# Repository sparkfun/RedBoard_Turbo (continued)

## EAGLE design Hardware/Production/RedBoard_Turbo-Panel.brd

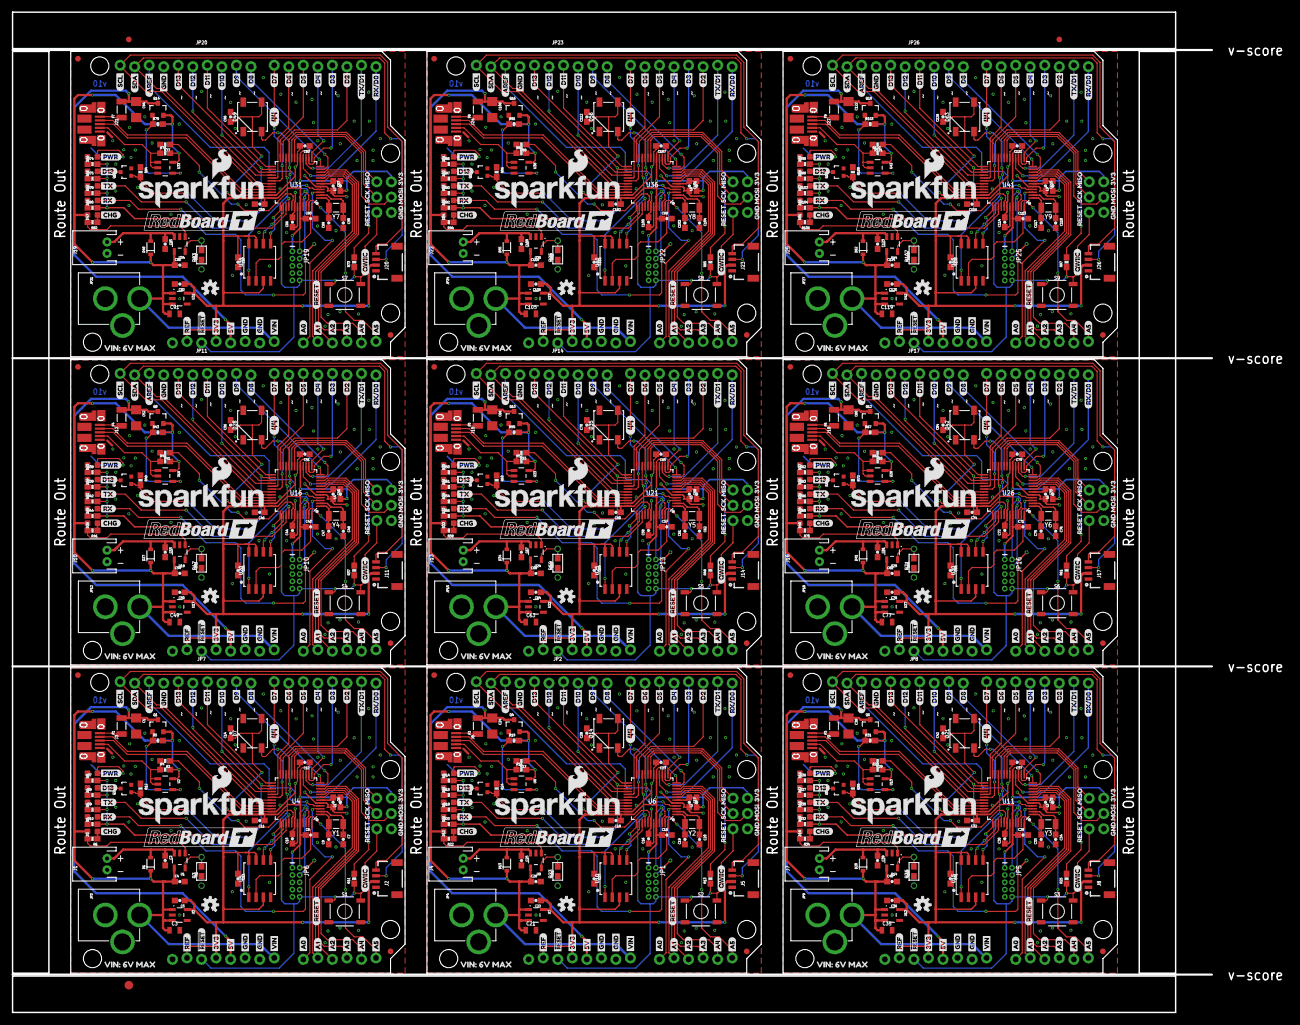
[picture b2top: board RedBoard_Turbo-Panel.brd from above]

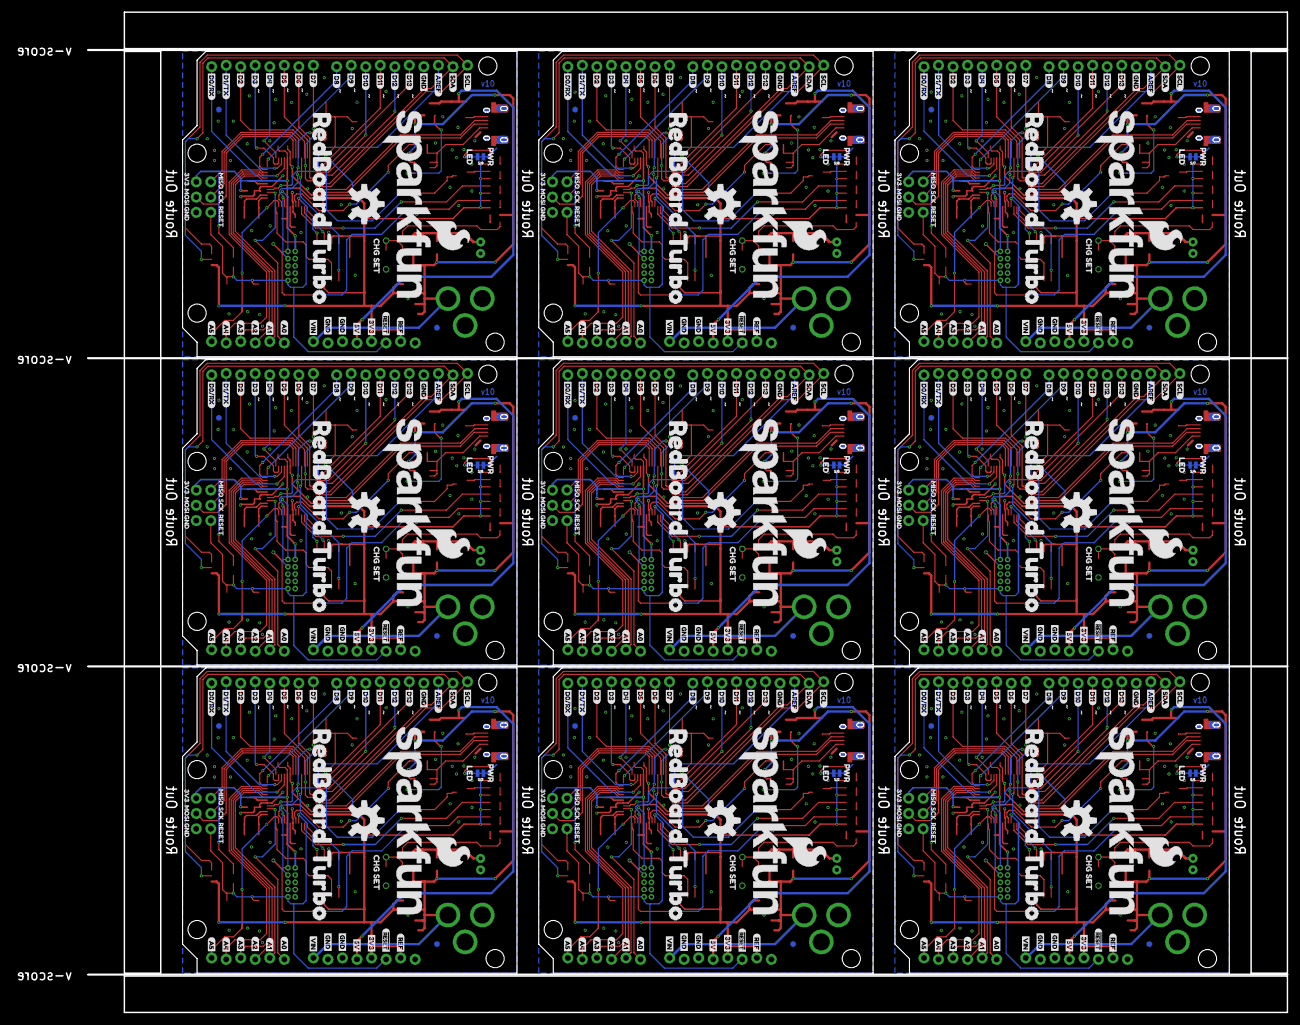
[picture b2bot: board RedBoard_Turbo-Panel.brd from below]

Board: 2 copper layers, 222.7 x 174.6 mm, 1335 parts (414 on the bottom side), 522 nets.

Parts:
C1, C24, C38, C52, C66, C80, C94, C108, C122: 2.2UF; 1206@1
C2, C4, C25, C26, C39, C40, C53, C54, C67, C68, C81, C82, C95, C96, C109, C110, C123, C124: 4.7uF; 0603-CAP
C3, C21, C35, C49, C63, C77, C91, C105, C119: 1.0uF; 0805
C5, C22, C36, C50, C64, C78, C92, C106, C120: 2.2uF; 0603-CAP
C6, C8, C10, C11, C12, C13, C14, C15, C16, C17, C18, C23, C27, C28, C29, C30, C31, C32, C37, C41, C42, C43, C44, C45, C46, C51, C55, C56, C57, C58, C59, C60, C65, C69, C70, C71, C72, C73, C74, C79, C83, C84, C85, C86, C87, C88, C93, C97, C98, C99, C100, C101, C102, C107, C111, C112, C113, C114, C115, C116, C121, C125, C126: 0.1uF; 0603-CAP
C7, C9, C19, C20, C33, C34, C47, C48, C61, C62, C75, C76, C89, C90, C103, C104, C117, C118: 15pF; 0603-CAP
D1, D13, D20, D27, D34, D41, D48, D55, D62: BAT20J; SOD-323
D2, D6, D11, D12, D18, D19, D25, D26, D32, D33, D39, D40, D46, D47, D53, D54, D60, D61: Yellow; LED-0603
D3, D9, D16, D23, D30, D37, D44, D51, D58: RED; LED-0603
D4, D10, D17, D24, D31, D38, D45, D52, D59: BLUE; LED-0603
D5, D8, D15, D22, D29, D36, D43, D50, D57: GREEN; LED-0603
D7, D14, D21, D28, D35, D42, D49, D56, D63: WS2812B
E$1, E$2: FIDUCIAL-1X2
E$3: FIDUCIAL-1.5X3
F1, F2, F3, F4, F5, F6, F7, F8, F9: 500mA; PTC-1206
FID1, FID2, FID3, FID4, FID5, FID6, FID7, FID8, FID9, FID10, FID11, FID12, FID13, FID14, FID15, FID16, FID17, FID18, FID19, FID20, FID21, FID22, FID23, FID24, FID25, FID26, FID27, FID28, FID29, FID30, FID31, FID32, FID33, FID34, FID35, FID36: FIDUCIAL1X2; FIDUCIAL-1X2
J1, J4, J7, J10, J13, J16, J19, J22, J25: JST-2-PTH
J2, J5, J8, J11, J14, J17, J20, J23, J26: 1X04_1MM_RA
J3, J6, J9, J12, J15, J18, J21, J24, J27: USB-MICROB-PTH-MILL
JP1, JP5, JP6, JP10, JP13, JP16, JP19, JP22, JP25: CORTEX_DEBUGPTH; 2X5-PTH-1.27MM
JP2, JP7, JP8, JP11, JP14, JP17, JP20, JP23, JP26: ARDUINO_UNO_R3LOCK_HOLES; ARDUINO_R3_LOCK_HOLES
JP3, JP4, JP9, JP12, JP15, JP18, JP21, JP24, JP27: POWER_JACKPTH; POWER_JACK_PTH
L1, L2, L3, L4, L5, L6, L7, L8, L9: FB - 30Ohm; 0603
LOGO1, LOGO6, LOGO10, LOGO14, LOGO18, LOGO22, LOGO26, LOGO30, LOGO34: SFE_LOGO_NAME_FLAME.2_INCH; SFE_LOGO_NAME_FLAME_.2
LOGO2, LOGO7, LOGO11, LOGO15, LOGO19, LOGO23, LOGO27, LOGO31, LOGO35: SFE_LOGO_NAME_FLAME.3_INCH; SFE_LOGO_NAME_FLAME_.3
LOGO3, LOGO5, LOGO9, LOGO13, LOGO17, LOGO21, LOGO25, LOGO29, LOGO33: OSHW-LOGOS; OSHW-LOGO-S
LOGO4, LOGO8, LOGO12, LOGO16, LOGO20, LOGO24, LOGO28, LOGO32, LOGO36: OSHW-LOGOL; OSHW-LOGO-L
Q1, Q4, Q6, Q8, Q10, Q12, Q14, Q16, Q18: 2.5A/30V; SOT23-3
Q2, Q3, Q5, Q7, Q9, Q11, Q13, Q15, Q17: 2N7002PW; SOT323
R1, R21, R33, R45, R57, R69, R81, R93, R105: 3.9K; 0603
R2, R6, R7, R8, R9, R10, R14, R15, R17, R18, R20, R22, R26, R27, R29, R30, R32, R34, R38, R39, R41, R42, R44, R46, R50, R51, R53, R54, R56, R58, R62, R63, R65, R66, R68, R70, R74, R75, R77, R78, R80, R82, R86, R87, R89, R90, R92, R94, R98, R99, R101, R102, R104, R106: 330; 0603-RES
R3, R23, R35, R47, R59, R71, R83, R95, R107: PROG; 1/6W-RES
R4, R12, R16, R24, R28, R36, R40, R48, R52, R60, R64, R72, R76, R84, R88, R96, R100, R108: 100k; 0603-RES
R5, R19, R31, R43, R55, R67, R79, R91, R103: 47K; 0603-RES
R11, R13, R25, R37, R49, R61, R73, R85, R97: 10K; 0603-RES
S1, S2, S3, S4, S5, S6, S7, S8, S9: TACTILE_SWITCH_SMD_5.2MM
SJ1, SJ2, SJ3, SJ4, SJ5, SJ6, SJ7, SJ8, SJ9: PWR-LED; PAD-JUMPER-2-NC_BY_TRACE_NO_SILK
TP1, TP2, TP3, TP4, TP5, TP6, TP7, TP8, TP9: TEST-POINTTP_15TH_THRU; TP_15TH
U1, U9, U14, U19, U24, U29, U34, U39, U44: MCP73831; SOT23-5
U2, U8, U13, U18, U23, U28, U33, U38, U43: 74AHC1G125; SOT23-5
U3, U7, U12, U17, U22, U27, U32, U37, U42: 3.3V; SOT23-5
U4, U6, U11, U16, U21, U26, U31, U36, U41: ATSAMD21G-A; TQFP-48
U5, U10, U15, U20, U25, U30, U35, U40, U45: W25Q32FV; SOIC-8
U$1, U$44, U$123, U$166, U$211, U$254, U$299, U$342, U$387, U$430, U$475, U$518, U$563, U$606, U$651, U$694, U$739, U$782: #RESET1
U$2, U$89, U$177, U$265, U$353, U$441, U$529, U$617, U$705: 3V317
U$3, U$90, U$178, U$266, U$354, U$442, U$530, U$618, U$706: 5V18
U$4, U$91, U$179, U$267, U$355, U$443, U$531, U$619, U$707: CHG30
U$5, U$92, U$180, U$268, U$356, U$444, U$532, U$620, U$708: RX#D015
U$6, U$93, U$181, U$269, U$357, U$445, U$533, U$621, U$709: TX#D114
U$7, U$94, U$182, U$270, U$358, U$446, U$534, U$622, U$710: D213
U$8, U$95, U$183, U$271, U$359, U$447, U$535, U$623, U$711: D312
U$9, U$96, U$184, U$272, U$360, U$448, U$536, U$624, U$712: D411
U$10, U$97, U$185, U$273, U$361, U$449, U$537, U$625, U$713: D510
U$11, U$98, U$186, U$274, U$362, U$450, U$538, U$626, U$714: D69
U$12, U$99, U$187, U$275, U$363, U$451, U$539, U$627, U$715: D78
U$13, U$100, U$188, U$276, U$364, U$452, U$540, U$628, U$716: D87
U$14, U$101, U$189, U$277, U$365, U$453, U$541, U$629, U$717: D96
U$15, U$102, U$190, U$278, U$366, U$454, U$542, U$630, U$718: D105
U$16, U$103, U$191, U$279, U$367, U$455, U$543, U$631, U$719: D114
U$17, U$104, U$192, U$280, U$368, U$456, U$544, U$632, U$720: D123
U$18, U$105, U$193, U$281, U$369, U$457, U$545, U$633, U$721: D132
U$19, U$36, U$37, U$106, U$121, U$122, U$194, U$209, U$210, U$282, U$297, U$298, U$370, U$385, U$386, U$458, U$473, U$474, U$546, U$561, U$562, U$634, U$649, U$650, U$722, U$737, U$738: GND16
U$20, U$81, U$107, U$164, U$195, U$252, U$283, U$340, U$371, U$428, U$459, U$516, U$547, U$604, U$635, U$692, U$723, U$780: SDA1
U$21, U$80, U$108, U$163, U$196, U$251, U$284, U$339, U$372, U$427, U$460, U$515, U$548, U$603, U$636, U$691, U$724, U$779: SCL0
U$22, U$109, U$197, U$285, U$373, U$461, U$549, U$637, U$725: TX28
U$23, U$110, U$198, U$286, U$374, U$462, U$550, U$638, U$726: RX29
U$24, U$111, U$199, U$287, U$375, U$463, U$551, U$639, U$727: PWR26
U$25, U$112, U$200, U$288, U$376, U$464, U$552, U$640, U$728: D1327
U$26, U$124, U$212, U$300, U$388, U$476, U$564, U$652, U$740: REF0
U$27, U$53, U$125, U$139, U$213, U$227, U$301, U$315, U$389, U$403, U$477, U$491, U$565, U$579, U$653, U$667, U$741, U$755: AREF2
U$28, U$113, U$201, U$289, U$377, U$465, U$553, U$641, U$729: QWIIC31
U$29, U$114, U$202, U$290, U$378, U$466, U$554, U$642, U$730: A020
U$30, U$115, U$203, U$291, U$379, U$467, U$555, U$643, U$731: A121
U$31, U$116, U$204, U$292, U$380, U$468, U$556, U$644, U$732: A222
U$32, U$117, U$205, U$293, U$381, U$469, U$557, U$645, U$733: A323
U$33, U$118, U$206, U$294, U$382, U$470, U$558, U$646, U$734: A424
U$34, U$119, U$207, U$295, U$383, U$471, U$559, U$647, U$735: A525
U$35, U$120, U$208, U$296, U$384, U$472, U$560, U$648, U$736: VIN19
U$38, U$126, U$214, U$302, U$390, U$478, U$566, U$654, U$742: GND7
U$39, U$127, U$215, U$303, U$391, U$479, U$567, U$655, U$743: MOSI4
U$40, U$128, U$216, U$304, U$392, U$480, U$568, U$656, U$744: 3V36
U$41, U$129, U$217, U$305, U$393, U$481, U$569, U$657, U$745: SCK5
U$42, U$130, U$218, U$306, U$394, U$482, U$570, U$658, U$746: MISO3
U$43, U$83, U$131, U$169, U$219, U$257, U$307, U$345, U$395, U$433, U$483, U$521, U$571, U$609, U$659, U$697, U$747, U$785: RESET0
U$45, U$132, U$220, U$308, U$396, U$484, U$572, U$660, U$748: 3V325
U$46, U$167, U$255, U$343, U$431, U$519, U$607, U$695, U$783: 3V30
U$47, U$133, U$221, U$309, U$397, U$485, U$573, U$661, U$749: A018
U$48, U$134, U$222, U$310, U$398, U$486, U$574, U$662, U$750: A119
U$49, U$135, U$223, U$311, U$399, U$487, U$575, U$663, U$751: A220
U$50, U$136, U$224, U$312, U$400, U$488, U$576, U$664, U$752: A321
U$51, U$137, U$225, U$313, U$401, U$489, U$577, U$665, U$753: A422
U$52, U$138, U$226, U$314, U$402, U$490, U$578, U$666, U$754: A523
U$54, U$174, U$262, U$350, U$438, U$526, U$614, U$702, U$790: LED1
U$55, U$140, U$228, U$316, U$404, U$492, U$580, U$668, U$756: D0#RX17
U$56, U$141, U$229, U$317, U$405, U$493, U$581, U$669, U$757: D1#TX15
U$57, U$168, U$256, U$344, U$432, U$520, U$608, U$696, U$784: 5V26
U$58, U$142, U$230, U$318, U$406, U$494, U$582, U$670, U$758: D79
U$59, U$143, U$231, U$319, U$407, U$495, U$583, U$671, U$759: D88
U$60, U$144, U$232, U$320, U$408, U$496, U$584, U$672, U$760: D97
U$61, U$145, U$233, U$321, U$409, U$497, U$585, U$673, U$761: D106
U$62, U$146, U$234, U$322, U$410, U$498, U$586, U$674, U$762: D115
U$63, U$147, U$235, U$323, U$411, U$499, U$587, U$675, U$763: D124
U$64, U$148, U$236, U$324, U$412, U$500, U$588, U$676, U$764: D133
U$65, U$149, U$237, U$325, U$413, U$501, U$589, U$677, U$765: D214
U$66, U$150, U$238, U$326, U$414, U$502, U$590, U$678, U$766: D313
U$67, U$151, U$239, U$327, U$415, U$503, U$591, U$679, U$767: D412
U$68, U$152, U$240, U$328, U$416, U$504, U$592, U$680, U$768: D511
U$69, U$153, U$241, U$329, U$417, U$505, U$593, U$681, U$769: D610
U$70, U$71, U$72, U$154, U$155, U$156, U$242, U$243, U$244, U$330, U$331, U$332, U$418, U$419, U$420, U$506, U$507, U$508, U$594, U$595, U$596, U$682, U$683, U$684, U$770, U$771, U$772: GND24
U$73, U$157, U$245, U$333, U$421, U$509, U$597, U$685, U$773: GND33
U$74, U$175, U$263, U$351, U$439, U$527, U$615, U$703, U$791: PWR0
U$75, U$158, U$246, U$334, U$422, U$510, U$598, U$686, U$774: MISO30
U$76, U$159, U$247, U$335, U$423, U$511, U$599, U$687, U$775: MOSI34
U$77, U$160, U$248, U$336, U$424, U$512, U$600, U$688, U$776: REF28
U$78, U$161, U$249, U$337, U$425, U$513, U$601, U$689, U$777: RESET32
U$79, U$162, U$250, U$338, U$426, U$514, U$602, U$690, U$778: SCK31
U$82, U$165, U$253, U$341, U$429, U$517, U$605, U$693, U$781: VIN27
U$84, U$171, U$259, U$347, U$435, U$523, U$611, U$699, U$787: 440
U$85, U$172, U$260, U$348, U$436, U$524, U$612, U$700, U$788: REDBOARD_TURBO1
U$86, U$170, U$258, U$346, U$434, U$522, U$610, U$698, U$786: BITMAP#JPG
U$87, U$173, U$261, U$349, U$437, U$525, U$613, U$701, U$789: CHG_SET1
U$88, U$176, U$264, U$352, U$440, U$528, U$616, U$704, U$792: VIN#_6V_MAX2
Y1, Y2, Y3, Y4, Y5, Y6, Y7, Y8, Y9: 32.768kHz; CRYSTAL-SMD-3.2X1.5MM

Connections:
3.3V: C5.1, C8.1, C11.1, C12.1, C13.1, C14.1, D7.1, J2.2, JP6.1, JP7.3.3V, JP7.IOREF, JP7.VCC, L1.1, R7.2, R8.2, R9.2, R10.2, R11.2, U3.5, U4.17, U4.36, U4.44, U5.3, U5.7, U5.8
3.3V1: C15.1, C18.1, C22.1, C23.1, C27.1, C28.1, D14.1, J5.2, JP1.1, JP2.3.3V, JP2.IOREF, JP2.VCC, L2.1, R13.2, R14.2, R15.2, R18.2, R20.2, U6.17, U6.36, U6.44, U7.5, U10.3, U10.7, U10.8
3.3V2: C29.1, C32.1, C36.1, C37.1, C41.1, C42.1, D21.1, J8.2, JP5.1, JP8.3.3V, JP8.IOREF, JP8.VCC, L3.1, R25.2, R26.2, R27.2, R30.2, R32.2, U11.17, U11.36, U11.44, U12.5, U15.3, U15.7, U15.8
3.3V3: C43.1, C46.1, C50.1, C51.1, C55.1, C56.1, D28.1, J11.2, JP10.1, JP11.3.3V, JP11.IOREF, JP11.VCC, L4.1, R37.2, R38.2, R39.2, R42.2, R44.2, U16.17, U16.36, U16.44, U17.5, U20.3, U20.7, U20.8
3.3V4: C57.1, C60.1, C64.1, C65.1, C69.1, C70.1, D35.1, J14.2, JP13.1, JP14.3.3V, JP14.IOREF, JP14.VCC, L5.1, R49.2, R50.2, R51.2, R54.2, R56.2, U21.17, U21.36, U21.44, U22.5, U25.3, U25.7, U25.8
3.3V5: C71.1, C74.1, C78.1, C79.1, C83.1, C84.1, D42.1, J17.2, JP16.1, JP17.3.3V, JP17.IOREF, JP17.VCC, L6.1, R61.2, R62.2, R63.2, R66.2, R68.2, U26.17, U26.36, U26.44, U27.5, U30.3, U30.7, U30.8
3.3V6: C85.1, C88.1, C92.1, C93.1, C97.1, C98.1, D49.1, J20.2, JP19.1, JP20.3.3V, JP20.IOREF, JP20.VCC, L7.1, R73.2, R74.2, R75.2, R78.2, R80.2, U31.17, U31.36, U31.44, U32.5, U35.3, U35.7, U35.8
3.3V7: C99.1, C102.1, C106.1, C107.1, C111.1, C112.1, D56.1, J23.2, JP22.1, JP23.3.3V, JP23.IOREF, JP23.VCC, L8.1, R85.2, R86.2, R87.2, R90.2, R92.2, U36.17, U36.36, U36.44, U37.5, U40.3, U40.7, U40.8
3.3V8: C113.1, C116.1, C120.1, C121.1, C125.1, C126.1, D63.1, J26.2, JP25.1, JP26.3.3V, JP26.IOREF, JP26.VCC, L9.1, R97.2, R98.2, R99.2, R102.2, R104.2, U41.17, U41.36, U41.44, U42.5, U45.3, U45.7, U45.8
!RESET: JP6.10, JP7.RESET@1, JP7.RESET@2, R11.1, S1.1, S1.2, U4.40
!RESET1: JP1.10, JP2.RESET@1, JP2.RESET@2, R13.1, S2.1, S2.2, U6.40
!RESET2: JP5.10, JP8.RESET@1, JP8.RESET@2, R25.1, S3.1, S3.2, U11.40
!RESET3: JP10.10, JP11.RESET@1, JP11.RESET@2, R37.1, S4.1, S4.2, U16.40
!RESET4: JP13.10, JP14.RESET@1, JP14.RESET@2, R49.1, S5.1, S5.2, U21.40
!RESET5: JP16.10, JP17.RESET@1, JP17.RESET@2, R61.1, S6.1, S6.2, U26.40
!RESET6: JP19.10, JP20.RESET@1, JP20.RESET@2, R73.1, S7.1, S7.2, U31.40
!RESET7: JP22.10, JP23.RESET@1, JP23.RESET@2, R85.1, S8.1, S8.2, U36.40
!RESET8: JP25.10, JP26.RESET@1, JP26.RESET@2, R97.1, S9.1, S9.2, U41.40
A0: JP7.A0, U4.3
A1: JP7.A1, U4.7
A2: JP7.A2, U4.8
A3: JP7.A3, U4.9
A4: JP7.A4, U4.10
A5: JP7.A5, U4.47
A6: JP2.A3, U6.9
A7: JP2.A2, U6.8
A8: JP2.A1, U6.7
A9: JP2.A0, U6.3
A10: JP2.A4, U6.10
A11: JP2.A5, U6.47
A12: JP8.A3, U11.9
A13: JP8.A2, U11.8
A14: JP8.A1, U11.7
A15: JP8.A0, U11.3
A16: JP8.A4, U11.10
A17: JP8.A5, U11.47
A18: JP11.A3, U16.9
A19: JP11.A2, U16.8
A20: JP11.A1, U16.7
A21: JP11.A0, U16.3
A22: JP11.A4, U16.10
A23: JP11.A5, U16.47
A24: JP14.A3, U21.9
A25: JP14.A2, U21.8
A26: JP14.A1, U21.7
A27: JP14.A0, U21.3
A28: JP14.A4, U21.10
A29: JP14.A5, U21.47
A30: JP17.A3, U26.9
A31: JP17.A2, U26.8
A32: JP17.A1, U26.7
A33: JP17.A0, U26.3
A34: JP17.A4, U26.10
A35: JP17.A5, U26.47
A36: JP20.A3, U31.9
A37: JP20.A2, U31.8
A38: JP20.A1, U31.7
A39: JP20.A0, U31.3
A40: JP20.A4, U31.10
A41: JP20.A5, U31.47
A42: JP23.A3, U36.9
A43: JP23.A2, U36.8
A44: JP23.A1, U36.7
A45: JP23.A0, U36.3
A46: JP23.A4, U36.10
A47: JP23.A5, U36.47
A48: JP26.A3, U41.9
A49: JP26.A2, U41.8
A50: JP26.A1, U41.7
A51: JP26.A0, U41.3
A52: JP26.A4, U41.10
A53: JP26.A5, U41.47
AREF: JP7.AREF, U4.4
AREF1: JP2.AREF, U6.4
AREF2: JP8.AREF, U11.4
AREF3: JP11.AREF, U16.4
AREF4: JP14.AREF, U21.4
AREF5: JP17.AREF, U26.4
AREF6: JP20.AREF, U31.4
AREF7: JP23.AREF, U36.4
AREF8: JP26.AREF, U41.4
CHG_STAT: R6.2, U1.1
CHG_STAT1: R22.2, U9.1
CHG_STAT2: R34.2, U14.1
CHG_STAT3: R46.2, U19.1
CHG_STAT4: R58.2, U24.1
CHG_STAT5: R70.2, U29.1
CHG_STAT6: R82.2, U34.1
CHG_STAT7: R94.2, U39.1
CHG_STAT8: R106.2, U44.1
D0/RXI: JP7.D0, U4.16
D0/RXI1: JP2.D0, U6.16
D0/RXI2: JP8.D0, U11.16
D0/RXI3: JP11.D0, U16.16
D0/RXI4: JP14.D0, U21.16
D0/RXI5: JP17.D0, U26.16
D0/RXI6: JP20.D0, U31.16
D0/RXI7: JP23.D0, U36.16
D0/RXI8: JP26.D0, U41.16
D1: JP2.D4, U6.13
D1/TXO: JP7.D1, U4.15
D1/TXO1: JP2.D1, U6.15
D1/TXO2: JP8.D1, U11.15
D1/TXO3: JP11.D1, U16.15
D1/TXO4: JP14.D1, U21.15
D1/TXO5: JP17.D1, U26.15
D1/TXO6: JP20.D1, U31.15
D1/TXO7: JP23.D1, U36.15
D1/TXO8: JP26.D1, U41.15
D2: JP7.D2, U4.23
D3: JP7.D3, U4.14
D4: JP7.D4, U4.13
D5: JP7.D5, U4.24
D6: JP7.D6, U4.29
D7: JP7.D7, U4.30
D8: JP7.D8, U4.11
D9: JP7.D9, U4.12
D10: JP7.D10, U4.27
D11: JP7.D11, U4.25
D12: JP7.D12, U4.28
D13: JP7.D13, Q2.1, R12.2, U4.26
D14: JP2.D3, U6.14
D15: JP2.D2, U6.23
D16: JP2.D5, U6.24
D17: JP2.D6, U6.29
D18: JP2.D7, U6.30
D19: JP2.D8, U6.11
D20: JP2.D9, U6.12
D21: JP2.D12, U6.28
D22: JP2.D11, U6.25
D23: JP2.D10, U6.27
D24: JP2.D13, Q3.1, R24.2, U6.26
D25: JP8.D4, U11.13
D26: JP8.D3, U11.14
D27: JP8.D2, U11.23
D28: JP8.D5, U11.24
D29: JP8.D6, U11.29
D30: JP8.D7, U11.30
D31: JP8.D8, U11.11
D32: JP8.D9, U11.12
D33: JP8.D12, U11.28
D34: JP8.D11, U11.25
D35: JP8.D10, U11.27
D36: JP8.D13, Q5.1, R36.2, U11.26
D37: JP11.D4, U16.13
D38: JP11.D3, U16.14
D39: JP11.D2, U16.23
D40: JP11.D5, U16.24
D41: JP11.D6, U16.29
D42: JP11.D7, U16.30
D43: JP11.D8, U16.11
D44: JP11.D9, U16.12
D45: JP11.D12, U16.28
D46: JP11.D11, U16.25
D47: JP11.D10, U16.27
D48: JP11.D13, Q7.1, R48.2, U16.26
D49: JP14.D4, U21.13
D50: JP14.D3, U21.14
D51: JP14.D2, U21.23
D52: JP14.D5, U21.24
D53: JP14.D6, U21.29
D54: JP14.D7, U21.30
D55: JP14.D8, U21.11
D56: JP14.D9, U21.12
D57: JP14.D12, U21.28
D58: JP14.D11, U21.25
D59: JP14.D10, U21.27
D60: JP14.D13, Q9.1, R60.2, U21.26
D61: JP17.D4, U26.13
D62: JP17.D3, U26.14
D63: JP17.D2, U26.23
D64: JP17.D5, U26.24
D65: JP17.D6, U26.29
D66: JP17.D7, U26.30
D67: JP17.D8, U26.11
D68: JP17.D9, U26.12
D69: JP17.D12, U26.28
D70: JP17.D11, U26.25
D71: JP17.D10, U26.27
D72: JP17.D13, Q11.1, R72.2, U26.26
D73: JP20.D4, U31.13
D74: JP20.D3, U31.14
D75: JP20.D2, U31.23
D76: JP20.D5, U31.24
D77: JP20.D6, U31.29
D78: JP20.D7, U31.30
D79: JP20.D8, U31.11
D80: JP20.D9, U31.12
D81: JP20.D12, U31.28
D82: JP20.D11, U31.25
D83: JP20.D10, U31.27
D84: JP20.D13, Q13.1, R84.2, U31.26
D85: JP23.D4, U36.13
D86: JP23.D3, U36.14
D87: JP23.D2, U36.23
D88: JP23.D5, U36.24
D89: JP23.D6, U36.29
D90: JP23.D7, U36.30
D91: JP23.D8, U36.11
D92: JP23.D9, U36.12
D93: JP23.D12, U36.28
D94: JP23.D11, U36.25
D95: JP23.D10, U36.27
D96: JP23.D13, Q15.1, R96.2, U36.26
D97: JP26.D4, U41.13
D98: JP26.D3, U41.14
D99: JP26.D2, U41.23
D100: JP26.D5, U41.24
D101: JP26.D6, U41.29
D102: JP26.D7, U41.30
D103: JP26.D8, U41.11
D104: JP26.D9, U41.12
D105: JP26.D12, U41.28
D106: JP26.D11, U41.25
D107: JP26.D10, U41.27
D108: JP26.D13, Q17.1, R108.2, U41.26
FLASH_CS: U4.22, U5.1
FLASH_CS1: U6.22, U10.1
FLASH_CS2: U11.22, U15.1
FLASH_CS3: U16.22, U20.1
FLASH_CS4: U21.22, U25.1
FLASH_CS5: U26.22, U30.1
FLASH_CS6: U31.22, U35.1
FLASH_CS7: U36.22, U40.1
FLASH_CS8: U41.22, U45.1
FLASH_MISO: U4.48, U5.2
FLASH_MISO1: U6.48, U10.2
FLASH_MISO2: U11.48, U15.2
FLASH_MISO3: U16.48, U20.2
FLASH_MISO4: U21.48, U25.2
FLASH_MISO5: U26.48, U30.2
FLASH_MISO6: U31.48, U35.2
FLASH_MISO7: U36.48, U40.2
FLASH_MISO8: U41.48, U45.2
FLASH_MOSI: U4.37, U5.5
FLASH_MOSI1: U6.37, U10.5
FLASH_MOSI2: U11.37, U15.5
FLASH_MOSI3: U16.37, U20.5
FLASH_MOSI4: U21.37, U25.5
FLASH_MOSI5: U26.37, U30.5
FLASH_MOSI6: U31.37, U35.5
FLASH_MOSI7: U36.37, U40.5
FLASH_MOSI8: U41.37, U45.5
FLASH_SCK: U4.38, U5.6
FLASH_SCK1: U6.38, U10.6
FLASH_SCK2: U11.38, U15.6
FLASH_SCK3: U16.38, U20.6
FLASH_SCK4: U21.38, U25.6
FLASH_SCK5: U26.38, U30.6
FLASH_SCK6: U31.38, U35.6
FLASH_SCK7: U36.38, U40.6
FLASH_SCK8: U41.38, U45.6
GND: C1.2, C2.2, C3.2, C4.2, C5.2, C6.2, C7.2, C8.2, C9.1, C10.2, C11.2, C12.2, C13.2, C14.2, D7.3, J1.1, J2.1, J3.GND, J3.SHIELD, J3.SHIELD2, J3.SHIELD3, J3.SHIELD4, J3.SHIELD5, J3.SHIELD6, J3.SHIELD7, J3.SHIELD8, J3.SHIELD9, J3.SHIELD10, JP3.GND, JP3.GNDBREAK, JP6.3, JP6.5, JP7.GND@1, JP7.GND@2, JP7.GND@3, JP7.GND@4, Q2.2, R1.1, R3.1, R12.1, S1.3, S1.4, SJ1.1, U1.2, U2.3, U3.2, U4.5, U4.18, U4.35, U4.42, U5.4
GND1: C15.2, C16.2, C17.2, C18.2, C19.1, C20.2, C21.2, C22.2, C23.2, C24.2, C25.2, C26.2, C27.2, C28.2, D14.3, J4.1, J5.1, J6.GND, J6.SHIELD, J6.SHIELD2, J6.SHIELD3, J6.SHIELD4, J6.SHIELD5, J6.SHIELD6, J6.SHIELD7, J6.SHIELD8, J6.SHIELD9, J6.SHIELD10, JP1.3, JP1.5, JP2.GND@1, JP2.GND@2, JP2.GND@3, JP2.GND@4, JP4.GND, JP4.GNDBREAK, Q3.2, R21.1, R23.1, R24.1, S2.3, S2.4, SJ2.1, U6.5, U6.18, U6.35, U6.42, U7.2, U8.3, U9.2, U10.4
GND2: C29.2, C30.2, C31.2, C32.2, C33.1, C34.2, C35.2, C36.2, C37.2, C38.2, C39.2, C40.2, C41.2, C42.2, D21.3, J7.1, J8.1, J9.GND, J9.SHIELD, J9.SHIELD2, J9.SHIELD3, J9.SHIELD4, J9.SHIELD5, J9.SHIELD6, J9.SHIELD7, J9.SHIELD8, J9.SHIELD9, J9.SHIELD10, JP5.3, JP5.5, JP8.GND@1, JP8.GND@2, JP8.GND@3, JP8.GND@4, JP9.GND, JP9.GNDBREAK, Q5.2, R33.1, R35.1, R36.1, S3.3, S3.4, SJ3.1, U11.5, U11.18, U11.35, U11.42, U12.2, U13.3, U14.2, U15.4
GND3: C43.2, C44.2, C45.2, C46.2, C47.1, C48.2, C49.2, C50.2, C51.2, C52.2, C53.2, C54.2, C55.2, C56.2, D28.3, J10.1, J11.1, J12.GND, J12.SHIELD, J12.SHIELD2, J12.SHIELD3, J12.SHIELD4, J12.SHIELD5, J12.SHIELD6, J12.SHIELD7, J12.SHIELD8, J12.SHIELD9, J12.SHIELD10, JP10.3, JP10.5, JP11.GND@1, JP11.GND@2, JP11.GND@3, JP11.GND@4, JP12.GND, JP12.GNDBREAK, Q7.2, R45.1, R47.1, R48.1, S4.3, S4.4, SJ4.1, U16.5, U16.18, U16.35, U16.42, U17.2, U18.3, U19.2, U20.4
GND4: C57.2, C58.2, C59.2, C60.2, C61.1, C62.2, C63.2, C64.2, C65.2, C66.2, C67.2, C68.2, C69.2, C70.2, D35.3, J13.1, J14.1, J15.GND, J15.SHIELD, J15.SHIELD2, J15.SHIELD3, J15.SHIELD4, J15.SHIELD5, J15.SHIELD6, J15.SHIELD7, J15.SHIELD8, J15.SHIELD9, J15.SHIELD10, JP13.3, JP13.5, JP14.GND@1, JP14.GND@2, JP14.GND@3, JP14.GND@4, JP15.GND, JP15.GNDBREAK, Q9.2, R57.1, R59.1, R60.1, S5.3, S5.4, SJ5.1, U21.5, U21.18, U21.35, U21.42, U22.2, U23.3, U24.2, U25.4
GND5: C71.2, C72.2, C73.2, C74.2, C75.1, C76.2, C77.2, C78.2, C79.2, C80.2, C81.2, C82.2, C83.2, C84.2, D42.3, J16.1, J17.1, J18.GND, J18.SHIELD, J18.SHIELD2, J18.SHIELD3, J18.SHIELD4, J18.SHIELD5, J18.SHIELD6, J18.SHIELD7, J18.SHIELD8, J18.SHIELD9, J18.SHIELD10, JP16.3, JP16.5, JP17.GND@1, JP17.GND@2, JP17.GND@3, JP17.GND@4, JP18.GND, JP18.GNDBREAK, Q11.2, R69.1, R71.1, R72.1, S6.3, S6.4, SJ6.1, U26.5, U26.18, U26.35, U26.42, U27.2, U28.3, U29.2, U30.4
GND6: C85.2, C86.2, C87.2, C88.2, C89.1, C90.2, C91.2, C92.2, C93.2, C94.2, C95.2, C96.2, C97.2, C98.2, D49.3, J19.1, J20.1, J21.GND, J21.SHIELD, J21.SHIELD2, J21.SHIELD3, J21.SHIELD4, J21.SHIELD5, J21.SHIELD6, J21.SHIELD7, J21.SHIELD8, J21.SHIELD9, J21.SHIELD10, JP19.3, JP19.5, JP20.GND@1, JP20.GND@2, JP20.GND@3, JP20.GND@4, JP21.GND, JP21.GNDBREAK, Q13.2, R81.1, R83.1, R84.1, S7.3, S7.4, SJ7.1, U31.5, U31.18, U31.35, U31.42, U32.2, U33.3, U34.2, U35.4
GND7: C99.2, C100.2, C101.2, C102.2, C103.1, C104.2, C105.2, C106.2, C107.2, C108.2, C109.2, C110.2, C111.2, C112.2, D56.3, J22.1, J23.1, J24.GND, J24.SHIELD, J24.SHIELD2, J24.SHIELD3, J24.SHIELD4, J24.SHIELD5, J24.SHIELD6, J24.SHIELD7, J24.SHIELD8, J24.SHIELD9, J24.SHIELD10, JP22.3, JP22.5, JP23.GND@1, JP23.GND@2, JP23.GND@3, JP23.GND@4, JP24.GND, JP24.GNDBREAK, Q15.2, R93.1, R95.1, R96.1, S8.3, S8.4, SJ8.1, U36.5, U36.18, U36.35, U36.42, U37.2, U38.3, U39.2, U40.4
GND8: C113.2, C114.2, C115.2, C116.2, C117.1, C118.2, C119.2, C120.2, C121.2, C122.2, C123.2, C124.2, C125.2, C126.2, D63.3, J25.1, J26.1, J27.GND, J27.SHIELD, J27.SHIELD2, J27.SHIELD3, J27.SHIELD4, J27.SHIELD5, J27.SHIELD6, J27.SHIELD7, J27.SHIELD8, J27.SHIELD9, J27.SHIELD10, JP25.3, JP25.5, JP26.GND@1, JP26.GND@2, JP26.GND@3, JP26.GND@4, JP27.GND, JP27.GNDBREAK, Q17.2, R105.1, R107.1, R108.1, S9.3, S9.4, SJ9.1, U41.5, U41.18, U41.35, U41.42, U42.2, U43.3, U44.2, U45.4
LED/SWCLK: D7.4, JP6.4, U4.45
LED/SWCLK1: D14.4, JP1.4, U6.45
LED/SWCLK2: D21.4, JP5.4, U11.45
LED/SWCLK3: D28.4, JP10.4, U16.45
LED/SWCLK4: D35.4, JP13.4, U21.45
LED/SWCLK5: D42.4, JP16.4, U26.45
LED/SWCLK6: D49.4, JP19.4, U31.45
LED/SWCLK7: D56.4, JP22.4, U36.45
LED/SWCLK8: D63.4, JP25.4, U41.45
unnamed: F1.1, J3.VBUS
unnamed: C9.2, U4.1, Y1.P$2
unnamed: D4.C, Q2.3
unnamed: C7.1, U4.2, Y1.P$1
unnamed: D3.A, R7.1
unnamed: D4.A, R8.1
unnamed: C19.2, U6.1, Y2.P$2
unnamed: D2.C, R6.1
unnamed: C20.1, U6.2, Y2.P$1
unnamed: D5.A, R9.1
unnamed: D6.A, R10.1
unnamed: D3.C, SJ1.2
unnamed: R1.2, R3.2, U1.5
unnamed: D9.A, R14.1
unnamed: D10.A, R15.1
unnamed: D10.C, Q3.3
unnamed: F2.1, J6.VBUS
unnamed: D8.A, R18.1
unnamed: D11.A, R20.1
unnamed: D9.C, SJ2.2
unnamed: R21.2, R23.2, U9.5
unnamed: D12.C, R22.1
unnamed: C33.2, U11.1, Y3.P$2
unnamed: C34.1, U11.2, Y3.P$1
unnamed: D16.A, R26.1
unnamed: D17.A, R27.1
unnamed: D17.C, Q5.3
unnamed: F3.1, J9.VBUS
unnamed: D15.A, R30.1
unnamed: D18.A, R32.1
unnamed: D16.C, SJ3.2
unnamed: R33.2, R35.2, U14.5
unnamed: D19.C, R34.1
unnamed: C47.2, U16.1, Y4.P$2
unnamed: C48.1, U16.2, Y4.P$1
unnamed: D23.A, R38.1
unnamed: D24.A, R39.1
unnamed: D24.C, Q7.3
unnamed: F4.1, J12.VBUS
unnamed: D22.A, R42.1
unnamed: D25.A, R44.1
unnamed: D23.C, SJ4.2
unnamed: R45.2, R47.2, U19.5
unnamed: D26.C, R46.1
unnamed: C61.2, U21.1, Y5.P$2
unnamed: C62.1, U21.2, Y5.P$1
unnamed: D30.A, R50.1
unnamed: D31.A, R51.1
unnamed: D31.C, Q9.3
unnamed: F5.1, J15.VBUS
unnamed: D29.A, R54.1
unnamed: D32.A, R56.1
unnamed: D30.C, SJ5.2
unnamed: R57.2, R59.2, U24.5
unnamed: D33.C, R58.1
unnamed: C75.2, U26.1, Y6.P$2
unnamed: C76.1, U26.2, Y6.P$1
unnamed: D37.A, R62.1
unnamed: D38.A, R63.1
unnamed: D38.C, Q11.3
unnamed: F6.1, J18.VBUS
unnamed: D36.A, R66.1
unnamed: D39.A, R68.1
unnamed: D37.C, SJ6.2
unnamed: R69.2, R71.2, U29.5
unnamed: D40.C, R70.1
unnamed: C89.2, U31.1, Y7.P$2
unnamed: C90.1, U31.2, Y7.P$1
unnamed: D44.A, R74.1
unnamed: D45.A, R75.1
unnamed: D45.C, Q13.3
unnamed: F7.1, J21.VBUS
unnamed: D43.A, R78.1
unnamed: D46.A, R80.1
unnamed: D44.C, SJ7.2
unnamed: R81.2, R83.2, U34.5
unnamed: D47.C, R82.1
unnamed: C103.2, U36.1, Y8.P$2
unnamed: C104.1, U36.2, Y8.P$1
unnamed: D51.A, R86.1
unnamed: D52.A, R87.1
unnamed: D52.C, Q15.3
unnamed: F8.1, J24.VBUS
unnamed: D50.A, R90.1
unnamed: D53.A, R92.1
unnamed: D51.C, SJ8.2
unnamed: R93.2, R95.2, U39.5
unnamed: D54.C, R94.1
unnamed: C117.2, U41.1, Y9.P$2
unnamed: C118.1, U41.2, Y9.P$1
unnamed: D58.A, R98.1
unnamed: D59.A, R99.1
unnamed: D59.C, Q17.3
unnamed: F9.1, J27.VBUS
unnamed: D57.A, R102.1
unnamed: D60.A, R104.1
unnamed: D58.C, SJ9.2
unnamed: R105.2, R107.2, U44.5
unnamed: D61.C, R106.1
RX_LED/SWDIO: D6.C, JP6.2, TP1.P$1, U4.46
RX_LED/SWDIO1: D11.C, JP1.2, TP2.P$1, U6.46
RX_LED/SWDIO2: D18.C, JP5.2, TP3.P$1, U11.46
RX_LED/SWDIO3: D25.C, JP10.2, TP4.P$1, U16.46
RX_LED/SWDIO4: D32.C, JP13.2, TP5.P$1, U21.46
RX_LED/SWDIO5: D39.C, JP16.2, TP6.P$1, U26.46
RX_LED/SWDIO6: D46.C, JP19.2, TP7.P$1, U31.46
RX_LED/SWDIO7: D53.C, JP22.2, TP8.P$1, U36.46
RX_LED/SWDIO8: D60.C, JP25.2, TP9.P$1, U41.46
SCL: J2.4, JP7.SCL, U4.32
SCL1: J5.4, JP2.SCL, U6.32
SCL2: J8.4, JP8.SCL, U11.32
SCL3: J11.4, JP11.SCL, U16.32
SCL4: J14.4, JP14.SCL, U21.32
SCL5: J17.4, JP17.SCL, U26.32
SCL6: J20.4, JP20.SCL, U31.32
SCL7: J23.4, JP23.SCL, U36.32
SCL8: J26.4, JP26.SCL, U41.32
SDA: J2.3, JP7.SDA, U4.31
SDA1: J5.3, JP2.SDA, U6.31
SDA2: J8.3, JP8.SDA, U11.31
SDA3: J11.3, JP11.SDA, U16.31
SDA4: J14.3, JP14.SDA, U21.31
SDA5: J17.3, JP17.SDA, U26.31
SDA6: J20.3, JP20.SDA, U31.31
SDA7: J23.3, JP23.SDA, U36.31
SDA8: J26.3, JP26.SDA, U41.31
SPI_MISO: JP7.MISO, U4.21
SPI_MISO1: JP2.MISO, U6.21
SPI_MISO2: JP8.MISO, U11.21
SPI_MISO3: JP11.MISO, U16.21
SPI_MISO4: JP14.MISO, U21.21
SPI_MISO5: JP17.MISO, U26.21
SPI_MISO6: JP20.MISO, U31.21
SPI_MISO7: JP23.MISO, U36.21
SPI_MISO8: JP26.MISO, U41.21
SPI_MOSI: JP7.MOSI, U4.19
SPI_MOSI1: JP2.MOSI, U6.19
SPI_MOSI2: JP8.MOSI, U11.19
SPI_MOSI3: JP11.MOSI, U16.19
SPI_MOSI4: JP14.MOSI, U21.19
SPI_MOSI5: JP17.MOSI, U26.19
SPI_MOSI6: JP20.MOSI, U31.19
SPI_MOSI7: JP23.MOSI, U36.19
SPI_MOSI8: JP26.MOSI, U41.19
SPI_SCK: JP7.SCK, U4.20
SPI_SCK1: JP2.SCK, U6.20
SPI_SCK2: JP8.SCK, U11.20
SPI_SCK3: JP11.SCK, U16.20
SPI_SCK4: JP14.SCK, U21.20
SPI_SCK5: JP17.SCK, U26.20
SPI_SCK6: JP20.SCK, U31.20
SPI_SCK7: JP23.SCK, U36.20
SPI_SCK8: JP26.SCK, U41.20
TX_LED: D5.C, U4.39
TX_LED1: D8.C, U6.39
TX_LED2: D15.C, U11.39
TX_LED3: D22.C, U16.39
TX_LED4: D29.C, U21.39
TX_LED5: D36.C, U26.39
TX_LED6: D43.C, U31.39
TX_LED7: D50.C, U36.39
TX_LED8: D57.C, U41.39
USB_D+: J3.D+, U4.34
USB_D+1: J6.D+, U6.34
USB_D+2: J9.D+, U11.34
USB_D+3: J12.D+, U16.34
USB_D+4: J15.D+, U21.34
USB_D+5: J18.D+, U26.34
USB_D+6: J21.D+, U31.34
USB_D+7: J24.D+, U36.34
USB_D+8: J27.D+, U41.34
USB_D-: J3.D-, U4.33
USB_D-1: J6.D-, U6.33
USB_D-2: J9.D-, U11.33
USB_D-3: J12.D-, U16.33
USB_D-4: J15.D-, U21.33
USB_D-5: J18.D-, U26.33
USB_D-6: J21.D-, U31.33
USB_D-7: J24.D-, U36.33
USB_D-8: J27.D-, U41.33
USB_HOST_EN: R2.1, U4.41
USB_HOST_EN1: R17.1, U6.41
USB_HOST_EN2: R29.1, U11.41
USB_HOST_EN3: R41.1, U16.41
USB_HOST_EN4: R53.1, U21.41
USB_HOST_EN5: R65.1, U26.41
USB_HOST_EN6: R77.1, U31.41
USB_HOST_EN7: R89.1, U36.41
USB_HOST_EN8: R101.1, U41.41
USB_HOST_POWER_EN: Q1.1, R5.1, U2.4
USB_HOST_POWER_EN1: Q4.1, R19.1, U8.4
USB_HOST_POWER_EN2: Q6.1, R31.1, U13.4
USB_HOST_POWER_EN3: Q8.1, R43.1, U18.4
USB_HOST_POWER_EN4: Q10.1, R55.1, U23.4
USB_HOST_POWER_EN5: Q12.1, R67.1, U28.4
USB_HOST_POWER_EN6: Q14.1, R79.1, U33.4
USB_HOST_POWER_EN7: Q16.1, R91.1, U38.4
USB_HOST_POWER_EN8: Q18.1, R103.1, U43.4
USB_ID: J3.ID, R2.2, R4.1, U2.1, U2.2
USB_ID1: J6.ID, R16.1, R17.2, U8.1, U8.2
USB_ID2: J9.ID, R28.1, R29.2, U13.1, U13.2
USB_ID3: J12.ID, R40.1, R41.2, U18.1, U18.2
USB_ID4: J15.ID, R52.1, R53.2, U23.1, U23.2
USB_ID5: J18.ID, R64.1, R65.2, U28.1, U28.2
USB_ID6: J21.ID, R76.1, R77.2, U33.1, U33.2
USB_ID7: J24.ID, R88.1, R89.2, U38.1, U38.2
USB_ID8: J27.ID, R100.1, R101.2, U43.1, U43.2
VBAT: C2.1, D1.A, J1.2, U1.3
VBAT1: C25.1, D13.A, J4.2, U9.3
VBAT2: C39.1, D20.A, J7.2, U14.3
VBAT3: C53.1, D27.A, J10.2, U19.3
VBAT4: C67.1, D34.A, J13.2, U24.3
VBAT5: C81.1, D41.A, J16.2, U29.3
VBAT6: C95.1, D48.A, J19.2, U34.3
VBAT7: C109.1, D55.A, J22.2, U39.3
VBAT8: C123.1, D62.A, J25.2, U44.3
VDDANA: C6.1, L1.2, U4.6
VDDANA1: C17.1, L2.2, U6.6
VDDANA2: C31.1, L3.2, U11.6
VDDANA3: C45.1, L4.2, U16.6
VDDANA4: C59.1, L5.2, U21.6
VDDANA5: C73.1, L6.2, U26.6
VDDANA6: C87.1, L7.2, U31.6
VDDANA7: C101.1, L8.2, U36.6
VDDANA8: C115.1, L9.2, U41.6
VDDCORE: C10.1, U4.43
VDDCORE1: C16.1, U6.43
VDDCORE2: C30.1, U11.43
VDDCORE3: C44.1, U16.43
VDDCORE4: C58.1, U21.43
VDDCORE5: C72.1, U26.43
VDDCORE6: C86.1, U31.43
VDDCORE7: C100.1, U36.43
VDDCORE8: C114.1, U41.43
VIN: C3.1, C4.1, D1.C, D2.A, JP3.PWR, JP7.VIN, Q1.2, R4.2, R5.2, U1.4, U2.5, U3.1, U3.3
VIN1: C21.1, C26.1, D12.A, D13.C, JP2.VIN, JP4.PWR, Q4.2, R16.2, R19.2, U7.1, U7.3, U8.5, U9.4
VIN2: C35.1, C40.1, D19.A, D20.C, JP8.VIN, JP9.PWR, Q6.2, R28.2, R31.2, U12.1, U12.3, U13.5, U14.4
VIN3: C49.1, C54.1, D26.A, D27.C, JP11.VIN, JP12.PWR, Q8.2, R40.2, R43.2, U17.1, U17.3, U18.5, U19.4
VIN4: C63.1, C68.1, D33.A, D34.C, JP14.VIN, JP15.PWR, Q10.2, R52.2, R55.2, U22.1, U22.3, U23.5, U24.4
VIN5: C77.1, C82.1, D40.A, D41.C, JP17.VIN, JP18.PWR, Q12.2, R64.2, R67.2, U27.1, U27.3, U28.5, U29.4
VIN6: C91.1, C96.1, D47.A, D48.C, JP20.VIN, JP21.PWR, Q14.2, R76.2, R79.2, U32.1, U32.3, U33.5, U34.4
VIN7: C105.1, C110.1, D54.A, D55.C, JP23.VIN, JP24.PWR, Q16.2, R88.2, R91.2, U37.1, U37.3, U38.5, U39.4
VIN8: C119.1, C124.1, D61.A, D62.C, JP26.VIN, JP27.PWR, Q18.2, R100.2, R103.2, U42.1, U42.3, U43.5, U44.4
VUSB: C1.1, F1.2, JP7.5V, Q1.3
VUSB1: C24.1, F2.2, JP2.5V, Q4.3
VUSB2: C38.1, F3.2, JP8.5V, Q6.3
VUSB3: C52.1, F4.2, JP11.5V, Q8.3
VUSB4: C66.1, F5.2, JP14.5V, Q10.3
VUSB5: C80.1, F6.2, JP17.5V, Q12.3
VUSB6: C94.1, F7.2, JP20.5V, Q14.3
VUSB7: C108.1, F8.2, JP23.5V, Q16.3
VUSB8: C122.1, F9.2, JP26.5V, Q18.3

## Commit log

2018-06-22 Initial revision changes
2018-06-22 Changed to RedBoard Turbo
2018-06-22 Added board title
2018-06-25 Add testpoint and label for LED
2018-06-25 Changes from review
2018-06-27 Change name on schematic
2018-06-27 Add polarity markings to JST connector
2018-07-09 Updated 0805 cap, approved DRC errors
2018-12-04 v20
    Updated silk
2018-12-06 Design Review Changes
    - Switched board version to v10
    - Changed RED charge LED to yellow
    - Updated power LED silk
    - Added barrel jack max voltage silk
    - Replaced reset button with larger button and longer actuator
2018-12-06 Updated schematic
    Updated part names and removed extra text
2018-12-07 panel
2019-01-24 Release Update
    -Updated README
    - Added .svg and .pdf graphical datasheets
    - Added .bin,.elf,.uf2 bootloader firmware
    - Added circuit python uf2 file
2019-01-28 Updated GDS
    Updated graphical data sheets
2019-10-04 Updating Datasheet per request
2021-01-14 Fix Minor Error in RedBoard Turbo SAMD21
    User found a minor error with a pin for the RedBoard Turbo SAMD21 => #4
    "GraphicalDatasheet-SamD21TurboDev.pdf should show RX_LED attached to pin PA31 not PB03. Schematic file shows RX_LED attached to pin PA31."
    It was verified and corrected. The pin characteristics were also updated with respect to the pin. Product page's documents and tutorial have been updated as well.
